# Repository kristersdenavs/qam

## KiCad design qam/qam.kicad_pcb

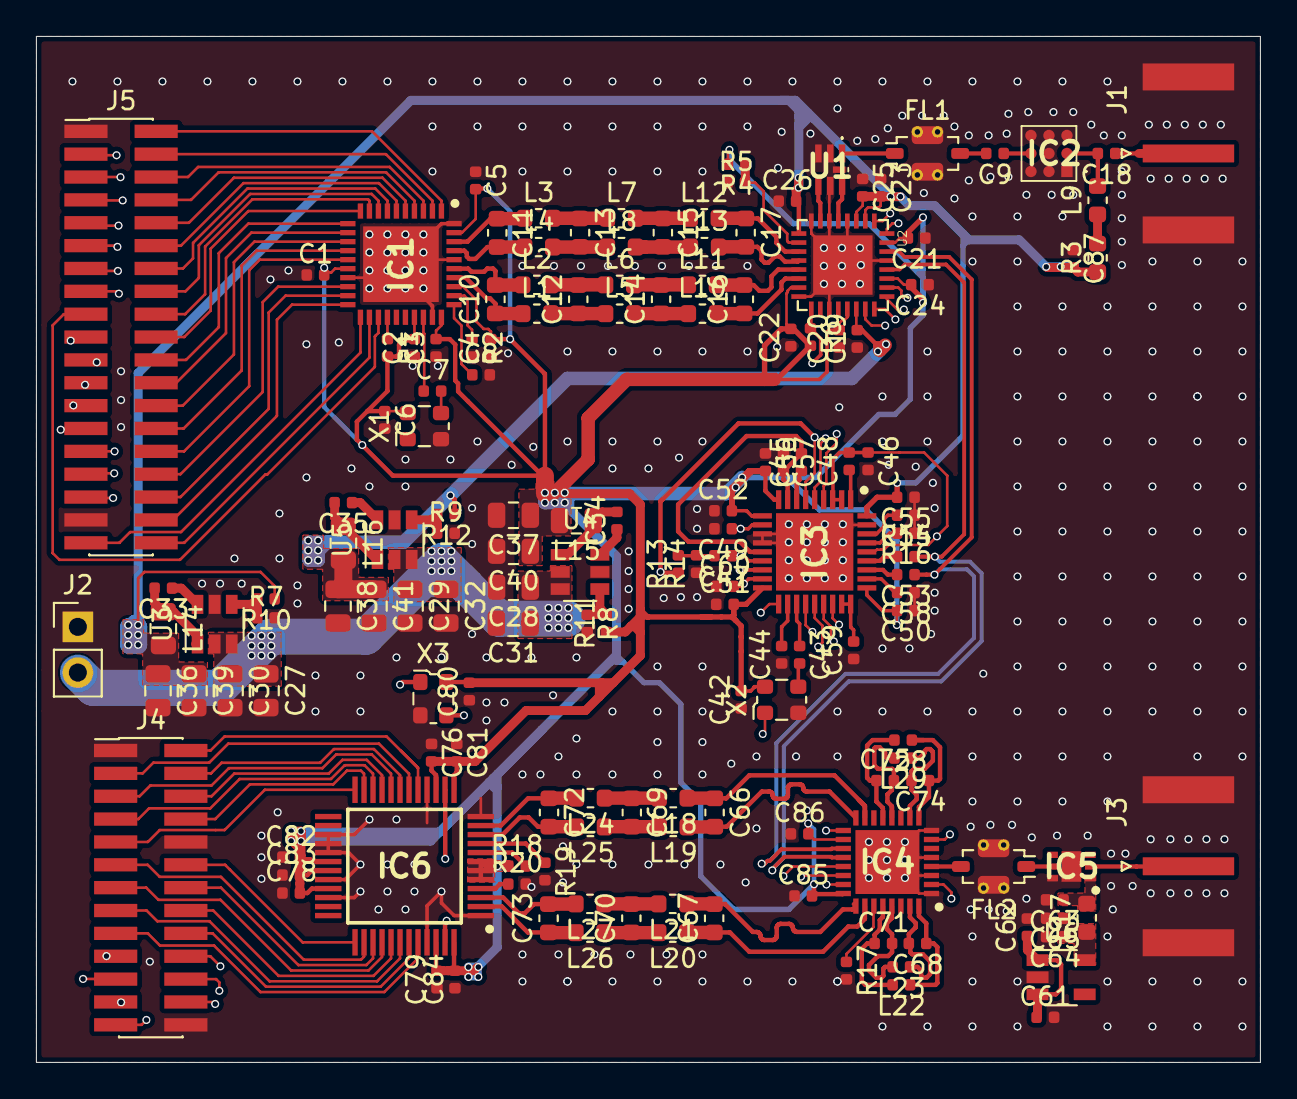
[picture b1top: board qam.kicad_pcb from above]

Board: 4 copper layers, 68.0 x 57.0 mm, 157 parts (0 on the bottom side), 152 nets.

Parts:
C1, C2, C3, C4, C5, C6, C7, C8, C9, C18, C19, C20, C21, C22, C23, C24, C25, C26, C42, C45, C46, C47, C48, C49, C50, C51, C52, C55, C56, C57, C58, C59, C60, C61, C62, C63, C64, C76, C78, C79, C80, C81, C82, C83, C84, C85, C86, C87: 0.1nF; C_0402_1005Metric
C10, C11, C12, C13, C14, C15, C16, C17, C66, C67, C69, C70, C72, C73: 470pF; C_0603_1608Metric
C27, C28, C29, C30, C31, C32, C36, C37, C38, C39, C40, C41: 10uF; C_0805_2012Metric
C33, C34, C35: 22nF; C_0402_1005Metric
C43, C44: 100pf; C_0402_1005Metric
C53, C54: 10pf; C_0402_1005Metric
C65: 1nF; C_0402_1005Metric
C68, C71, C74, C75: 470pF; C_0402_1005Metric
FL1, FL2: LFCN-8400; Filter_Mini-Circuits_FV1206-4
IC1: MAX5854ETL+; QFN50P600X600X80-41N
IC2: NBB-402-T1; NBB402T1
IC3: STUW81300TR; QFN50P600X600X100-37N-D
IC4: LTC5594IUH#PBF; QFN50P500X500X80-33N-D
IC5: HMC8411LP2FE; SON65P200X200X90-7N-D
IC6: AD9288BSTZ-100; QFP50P900X900X160-48N
J1, J3: Conn_Coaxial; SMA_Amphenol_132289_EdgeMount
J2: con; PinHeader_1x02_P2.54mm_Vertical
J4: 02x13; PinHeader_2x13_P1.27mm_Vertical_SMD
J5: 02x19; PinHeader_2x19_P1.27mm_Vertical_SMD
L1, L2, L3, L4, L5, L6, L7, L8, L9, L10, L11, L12, L13, L17, L18, L19, L20, L21, L24, L25, L26, L27: 250nH; L_0603_1608Metric
L14, L15, L16: 4.7uH; L_0805_2012Metric
L22, L23, L28, L29: 250nH; L_0402_1005Metric
R1, R2, R4, R5, R6, R13, R14, R17, R18, R19, R20: 25k; R_0402_1005Metric
R3: 22; R_0603_1608Metric
R7: 9.53k; R_0402_1005Metric
R8: 16k; R_0402_1005Metric
R9: 40k; R_0402_1005Metric
R10, R11, R12: 49.9k; R_0402_1005Metric
R15, R16: 50; R_0402_1005Metric
U1: NCS2-83+; NCS283
U2: ADRF6780ACPZN-R7; QFN50P500X500X80-33N330X330
U3, U4, U5: ACT4088US; SOT-23-6
U6: NCV8114BSN300T1G; TSOT-23-5
X1, X2, X3: 25 MHz TCXO; Oscillator_SMD_ECS_2520MV-xxx-xx-4Pin_2.5x2.0mm

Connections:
+1V8: C19.2, C38.1, C41.1, L16.2, R12.1, U2.22
+3V3: C1.2, C2.2, C3.2, C4.2, C5.2, C6.1, C20.2, C21.2, C22.2, C24.2, C37.1, C40.1, C42.2, C50.2, C51.2, C52.2, C56.2, C76.2, C78.2, C79.2, C80.2, C81.2, C82.2, C83.2, C84.2, C85.2, C86.2, IC1.16, IC1.27, IC1.30, IC1.33, IC1.39, IC3.9, IC3.10, IC3.18, IC3.28, IC4.18, IC4.24, IC6.5, IC6.6, IC6.7, IC6.13, IC6.15, IC6.30, IC6.31, IC6.33, IC6.46, IC6.48, L15.2, R1.2, R4.2, R6.2, R11.1, R18.1, U2.15, U2.21, U2.27, U2.31, X1.4, X2.4, X3.4
+5V: C23.2, C25.2, C26.2, C36.1, C39.1, C55.2, C87.2, IC3.36, L14.2, R3.1, R10.1, U2.2, U2.3, U2.9
+24V: C27.1, C28.1, C29.1, C30.1, C31.1, C32.1, J2.2, U3.2, U3.3, U4.2, U4.3, U5.2, U5.3
/dem/ADC_CLK_OUT: IC6.14, IC6.47, X3.3
/dem/AIM: C71.2, IC4.29, L23.2
/dem/AIP: C71.1, IC4.28, L22.2
/dem/AMPD: IC4.27, R17.1
/dem/ANT_IN: IC5.2, J3.1
/dem/AQM: C75.2, IC4.12, L29.2
/dem/AQP: C75.1, IC4.13, L28.2
/dem/DFS: IC6.4, R20.1
/dem/I_N: C66.2, IC4.16, L19.1
/dem/I_NF: C72.2, IC6.10, L25.2
/dem/I_P: C66.1, IC4.15, L18.1
/dem/I_PF: C72.1, IC6.11, L24.2
/dem/LNA_BIAS: C64.1, C65.1, L17.1, U6.5
/dem/LNA_OUT: FL2.1, IC5.5
/dem/LPF_OUT: FL2.3, IC4.4
/dem/MIM: C68.2, IC4.31, L23.1
/dem/MIP: C68.1, IC4.32, L22.1
/dem/MQM: C74.2, IC4.10, L29.1
/dem/MQP: C74.1, IC4.9, L28.1
/dem/Q_N: C67.2, IC4.25, L21.1
/dem/Q_NF: C73.2, IC6.3, L27.2
/dem/Q_P: C67.1, IC4.26, L20.1
/dem/Q_PF: C73.1, IC6.2, L26.2
/dem/S1: IC6.8, R18.2
/dem/S2: IC6.9, R19.1
/mod/DAC_CLK: C7.1, IC1.28
/mod/I_N: C11.2, IC1.37, L4.1
/mod/I_NF: C16.1, L10.2, U2.14
/mod/I_P: C11.1, IC1.38, L3.1
/mod/I_PF: C16.2, L11.2, U2.13
/mod/LPF_OUT: C9.2, FL1.3
/mod/MOD_VATT: R4.1, R5.2, U2.10
/mod/Q_N: C10.1, IC1.34, L1.1
/mod/Q_NF: C17.1, L12.2, U2.11
/mod/Q_P: C10.2, IC1.35, L2.1
/mod/Q_PF: C17.2, L13.2, U2.12
/mod/RF_N_OUT: U1.4, U2.7
/mod/RF_OUT: C18.1, J1.1
/mod/RF_P_OUT: U1.6, U2.5
/mod/RF_UN_OUT: FL1.1, U1.1
/mod/~DCE: IC1.24, R1.1
/synth/LO_REFN_OUT: C44.2, IC3.20
/synth/LO_REFP_OUT: C43.1, IC3.21
/synth/RF_OUT_N: C54.1, IC3.31
/synth/RF_OUT_P: C53.2, IC3.30
/synth/SYN_VDD_PFD: C60.2, IC3.17, IC3.19
/synth/SYN_VREG_DIG: C59.2, IC3.26, IC3.27
/synth/SYN_VREG_RF: C58.2, IC3.29
/synth/VREG_VCO: C45.2, C57.2, IC3.8, IC3.14
ADC_CLK_ENABLE: J4.20, X3.1
ADC_D0A: IC6.37, J4.12
ADC_D0B: IC6.24, J4.9
ADC_D1A: IC6.38, J4.11
ADC_D1B: IC6.23, J4.8
ADC_D2A: IC6.39, J4.14
ADC_D2B: IC6.22, J4.7
ADC_D3A: IC6.40, J4.13
ADC_D3B: IC6.21, J4.6
ADC_D4A: IC6.41, J4.16
ADC_D4B: IC6.20, J4.5
ADC_D5A: IC6.42, J4.15
ADC_D5B: IC6.19, J4.4
ADC_D6A: IC6.43, J4.18
ADC_D6B: IC6.18, J4.3
ADC_D7A: IC6.44, J4.17
ADC_D7B: IC6.17, J4.2
DAC_CW: IC1.23, J5.17
DAC_DA0: IC1.10, J5.20
DAC_DA1: IC1.9, J5.18
DAC_DA2: IC1.8, J5.16
DAC_DA3: IC1.7, J5.14
DAC_DA4: IC1.6, J5.12
DAC_DA5: IC1.5, J5.10
DAC_DA6: IC1.4, J5.8
DAC_DA7: IC1.3, J5.6
DAC_DA8: IC1.2, J5.4
DAC_DA9: IC1.1, J5.2
DAC_DB0: IC1.22, J5.38
DAC_DB1: IC1.21, J5.37
DAC_DB2: IC1.20, J5.36
DAC_DB3: IC1.19, J5.34
DAC_DB4: IC1.18, J5.32
DAC_DB5: IC1.15, J5.30
DAC_DB6: IC1.14, J5.28
DAC_DB7: IC1.13, J5.26
DAC_DB8: IC1.12, J5.24
DAC_DB9: IC1.11, J5.22
DEM_CS: IC4.17, J4.23
DEM_EN: IC4.7, J4.21
DEM_SCK: IC4.23, J4.24
DEM_SDI: IC4.22, J4.22
DEM_SDO: IC4.21, J4.25
DEM_TEMP: IC4.2, J4.19
GND: C1.1, C2.1, C3.1, C4.1, C5.1, C6.2, C8.2, C19.1, C20.1, C21.1, C22.1, C23.1, C24.1, C25.1, C26.1, C27.2, C28.2, C29.2, C30.2, C31.2, C32.2, C36.2, C37.2, C38.2, C39.2, C40.2, C41.2, C42.1, C44.1, C46.2, C49.2, C50.1, C51.1, C52.1, C55.1, C56.1, C57.1, C58.1, C59.1, C60.1, C61.2, C62.2, C63.2, C64.2, C65.2, C76.1, C78.1, C79.1, C80.1, C81.1, C82.1, C83.1, C84.1, C85.1, C86.1, C87.1, FL1.2, FL1.4, FL2.2, FL2.4, IC1.17, IC1.29, IC1.36, IC1.40, IC1.41, IC2.1, IC2.2, IC2.3, IC2.5, IC2.6, IC2.7, IC2.9, IC3.12, IC3.13, IC3.35, IC3.37, IC4.1, IC4.3, IC4.5, IC4.8, IC4.33, IC5.6, IC5.7, IC6.1, IC6.12, IC6.16, IC6.27, IC6.28, IC6.29, IC6.32, IC6.34, IC6.45, J1.2, J2.1, J3.2, J4.1, J4.10, J4.26, J5.1, J5.35, R2.2, R5.1, R7.2, R8.2, R9.2, R14.1, R15.1, R16.1, R17.2, R19.2, R20.2, U1.2, U1.3, U1.5, U1.7, U2.4, U2.6, U2.8, U2.16, U2.19, U2.29, U2.33, U3.5, U4.5, U5.5, U6.2, X1.2, X2.2, X3.2
LO_N: C54.2, IC4.20, U2.28
LO_P: C53.1, IC4.19, U2.30
LO_REF_EN: J5.19, X2.1
MOD_ALM: J5.7, U2.32
MOD_CS: J5.3, U2.26
MOD_RST: J5.15, R6.1, U2.17
MOD_SCK: J5.11, U2.24
MOD_SDI: J5.13, U2.23
MOD_SDO: J5.9, U2.25
MOD_VDET: J5.5, U2.1
unnamed: C7.2, X1.3
unnamed: C8.1, IC1.31
unnamed: C9.1, IC2.4
unnamed: C12.1, L1.2, L5.1
unnamed: C12.2, L2.2, L6.1
unnamed: C13.1, L3.2, L7.1
unnamed: C13.2, L4.2, L8.1
unnamed: C14.1, L5.2, L10.1
unnamed: C14.2, L6.2, L11.1
unnamed: C15.1, L7.2, L12.1
unnamed: C15.2, L8.2, L13.1
unnamed: C18.2, IC2.8, L9.2
unnamed: C33.1, U3.6
unnamed: C33.2, L14.1, U3.1
unnamed: C34.1, U4.6
unnamed: C34.2, L15.1, U4.1
unnamed: C35.1, U5.6
unnamed: C35.2, L16.1, U5.1
unnamed: C43.2, X2.3
unnamed: C45.1, IC3.7
unnamed: C46.1, C48.2, IC3.2, IC3.3, IC3.16, IC3.32
unnamed: C47.1, C49.1, IC3.11, IC3.15
unnamed: C47.2, R13.2, R14.2
unnamed: C48.1, IC3.1
unnamed: C63.1, IC5.1, L17.2
unnamed: C69.1, L18.2, L24.1
unnamed: C69.2, L19.2, L25.1
unnamed: C70.1, L20.2, L26.1
unnamed: C70.2, L21.2, L27.1
unnamed: IC1.32, R2.1
unnamed: IC3.33, R16.2
unnamed: IC3.34, R15.2
unnamed: L9.1, R3.2
unnamed: R7.1, R10.2, U3.4
unnamed: R8.1, R11.2, U4.4
unnamed: R9.1, R12.2, U5.4
SYN_CS: IC3.25, J5.21
SYN_EN: IC3.4, J5.29
SYN_PDRF1: IC3.5, J5.31
SYN_PDRF2: IC3.6, J5.33, R13.1
SYN_SCK: IC3.24, J5.23
SYN_SDI: IC3.23, J5.25
SYN_SDO: IC3.22, J5.27
VDD: C61.1, C62.1, U6.1, U6.3

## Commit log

2020-12-16 Added EVERYTHING
